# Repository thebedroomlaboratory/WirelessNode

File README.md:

WirelessNode
============

Common code for wireless home automation nodes

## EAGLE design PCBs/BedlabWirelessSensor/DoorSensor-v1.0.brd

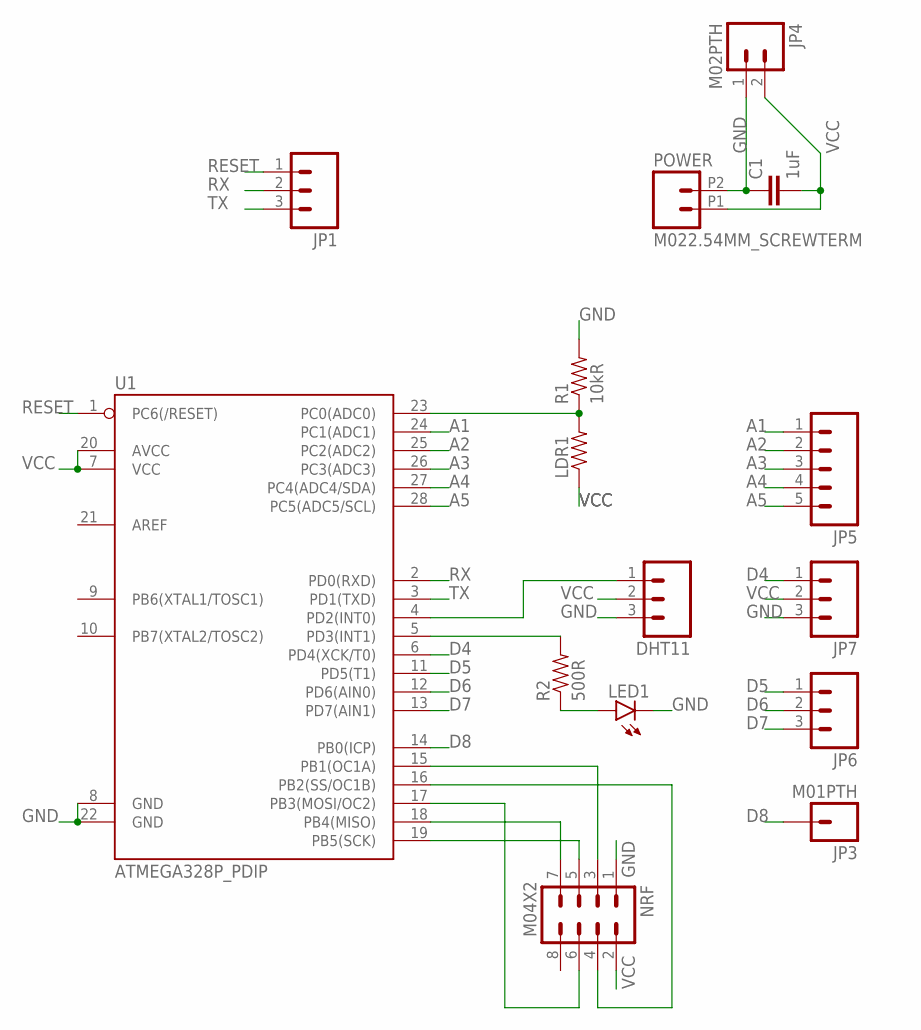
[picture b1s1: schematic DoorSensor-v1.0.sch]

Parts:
C1: 1uF; CAP-PTH-SMALL
DHT11: M03PTH; 1X03
JP1, JP6, JP7: M03PTH; 1X03
JP3: M01PTH; 1X01
JP4: M02PTH; 1X02
JP5: M05PTH; 1X05
LDR1: RESISTORKIT; AXIAL-0.3-KIT
LED1: LED3MM
NRF: M04X2; 2X4
POWER: M022.54MM_SCREWTERM; 1X02_2.54_SCREWTERM
R1: 10kR; AXIAL-0.3-KIT
R2: 500R; AXIAL-0.3-KIT
U1: ATMEGA328P_PDIP; DIL28-3

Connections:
A1: JP5.1, U1.24 (PC1(ADC1))
A2: JP5.2, U1.25 (PC2(ADC2))
A3: JP5.3, U1.26 (PC3(ADC3))
A4: JP5.4, U1.27 (PC4(ADC4/SDA))
A5: JP5.5, U1.28 (PC5(ADC5/SCL))
D4: JP7.1, U1.6 (PD4(XCK/T0))
D5: JP6.1, U1.11 (PD5(T1))
D6: JP6.2, U1.12 (PD6(AIN0))
D7: JP6.3, U1.13 (PD7(AIN1))
D8: JP3.1, U1.14 (PB0(ICP))
GND: C1.1, DHT11.3, JP4.1, JP7.3, LED1.K (C), NRF.1, POWER.P2 (2), R1.P$2 (2), U1.8 (GND), U1.22 (GND)
unnamed: LDR1.P$2 (2), R1.P$1 (1), U1.23 (PC0(ADC0))
unnamed: LED1.A, R2.P$1 (1)
unnamed: DHT11.1, U1.4 (PD2(INT0))
unnamed: R2.P$2 (2), U1.5 (PD3(INT1))
unnamed: NRF.3, U1.15 (PB1(OC1A))
unnamed: NRF.4, U1.16 (PB2(SS/OC1B))
unnamed: NRF.5, U1.19 (PB5(SCK))
unnamed: NRF.7, U1.18 (PB4(MISO))
unnamed: NRF.6, U1.17 (PB3(MOSI/OC2))
RESET: JP1.1, U1.1 (PC6(/RESET))
RX: JP1.2, U1.2 (PD0(RXD))
TX: JP1.3, U1.3 (PD1(TXD))
VCC: C1.2, DHT11.2, JP4.2, JP7.2, LDR1.P$1 (1), NRF.2, POWER.P1 (1), U1.7 (VCC), U1.20 (AVCC)

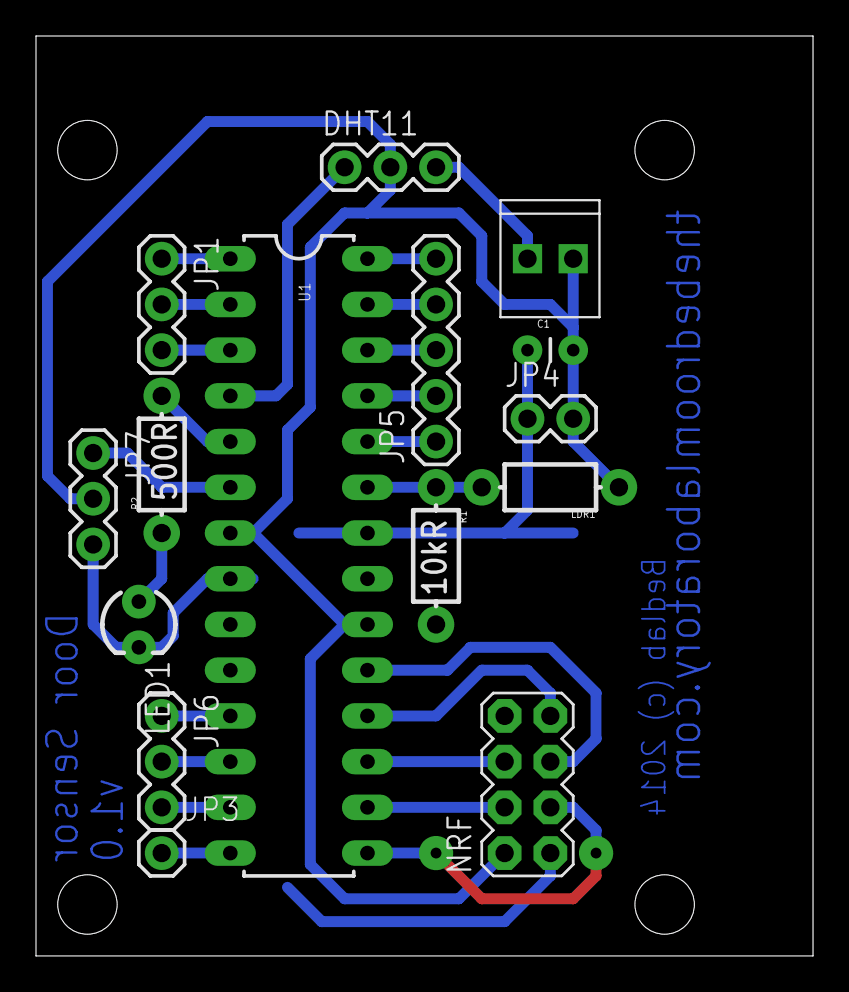
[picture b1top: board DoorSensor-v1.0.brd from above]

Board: 2 copper layers, 43.2 x 51.1 mm, 19 parts (0 on the bottom side), 24 nets.

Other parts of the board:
U$1, U$2, U$3, U$4: STAND-OFF

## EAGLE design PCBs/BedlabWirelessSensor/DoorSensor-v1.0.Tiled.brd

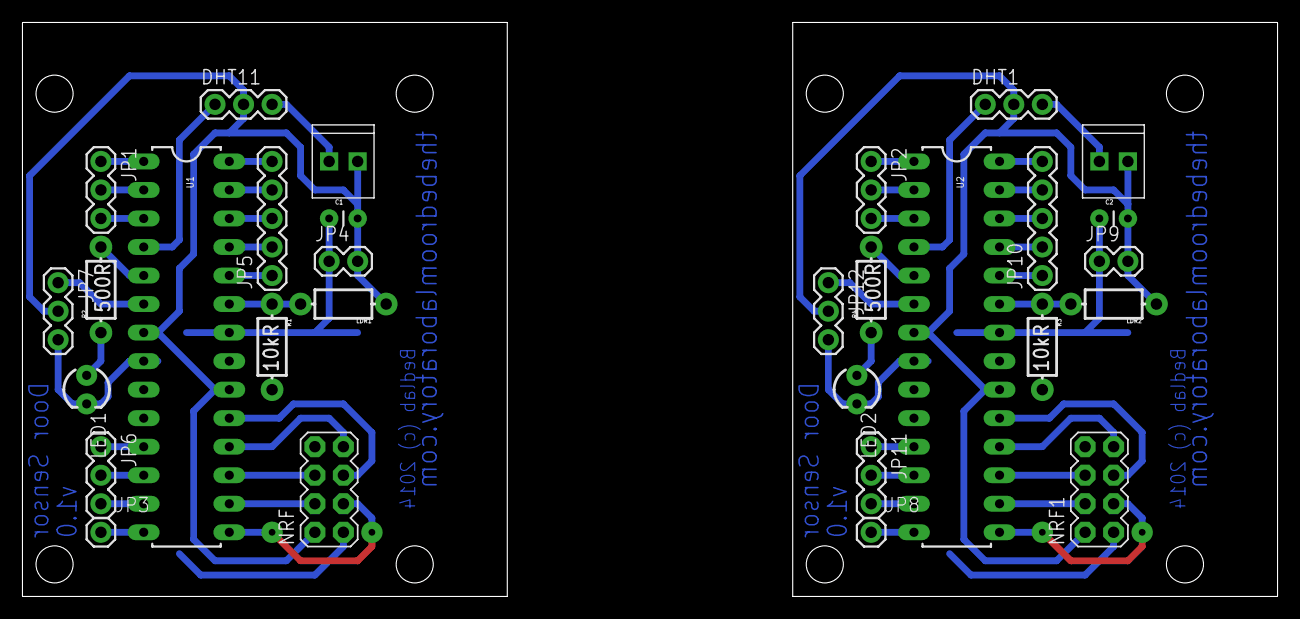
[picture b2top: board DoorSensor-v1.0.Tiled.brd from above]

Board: 2 copper layers, 111.7 x 51.1 mm, 38 parts (0 on the bottom side), 48 nets.

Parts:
C1, C2: 1uF; CAP-PTH-SMALL
DHT1, DHT11: 1X03
JP1, JP2, JP6, JP7, JP11, JP12: 1X03
JP3, JP8: M01PTH; 1X01
JP4, JP9: M02PTH; 1X02
JP5, JP10: 1X05
LDR1, LDR2: AXIAL-0.3-KIT
LED1, LED2: LED3MM
NRF, NRF1: M04X2; 2X4
POWER, POWER1: M022.54MM_SCREWTERM; 1X02_2.54_SCREWTERM
R1, R3: 10kR; AXIAL-0.3-KIT
R2, R4: 500R; AXIAL-0.3-KIT
U1, U2: ATMEGA328P_PDIP; DIL28-3
U$1, U$2, U$3, U$4, U$5, U$6, U$7, U$8: STAND-OFF

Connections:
A1: JP5.1, U1.24
A2: JP5.2, U1.25
A3: JP5.3, U1.26
A4: JP5.4, U1.27
A5: JP5.5, U1.28
A6: JP10.1, U2.24
A7: JP10.2, U2.25
A8: JP10.3, U2.26
A9: JP10.4, U2.27
A10: JP10.5, U2.28
D1: JP8.1, U2.14
D2: JP12.1, U2.6
D3: JP11.1, U2.11
D4: JP7.1, U1.6
D5: JP6.1, U1.11
D6: JP6.2, U1.12
D7: JP6.3, U1.13
D8: JP3.1, U1.14
D9: JP11.2, U2.12
D10: JP11.3, U2.13
GND: C1.1, DHT11.3, JP4.1, JP7.3, LED1.K, NRF.1, POWER.P2, R1.P$2, U1.8, U1.22
GND1: C2.1, DHT1.3, JP9.1, JP12.3, LED2.K, NRF1.1, POWER1.P2, R3.P$2, U2.8, U2.22
unnamed: LDR1.P$2, R1.P$1, U1.23
unnamed: LED1.A, R2.P$1
unnamed: DHT11.1, U1.4
unnamed: R2.P$2, U1.5
unnamed: NRF.3, U1.15
unnamed: NRF.4, U1.16
unnamed: NRF.5, U1.19
unnamed: LDR2.P$2, R3.P$1, U2.23
unnamed: NRF.7, U1.18
unnamed: NRF.6, U1.17
unnamed: LED2.A, R4.P$1
unnamed: R4.P$2, U2.5
unnamed: NRF1.3, U2.15
unnamed: NRF1.4, U2.16
unnamed: NRF1.5, U2.19
unnamed: NRF1.7, U2.18
unnamed: NRF1.6, U2.17
unnamed: DHT1.1, U2.4
RESET: JP1.1, U1.1
RESET1: JP2.1, U2.1
RX: JP1.2, U1.2
RX1: JP2.2, U2.2
TX: JP1.3, U1.3
TX1: JP2.3, U2.3
VCC: C1.2, DHT11.2, JP4.2, JP7.2, LDR1.P$1, NRF.2, POWER.P1, U1.7, U1.20
VCC1: C2.2, DHT1.2, JP9.2, JP12.2, LDR2.P$1, NRF1.2, POWER1.P1, U2.7, U2.20

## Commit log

2014-07-19 Very rough first commit for arduino wireless sensors. The structure of the sketch is that there should be a profile for each type of sensor and each node is setup for wireless connectivity too, on th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
    Code needs a good bit of tidying and fixing but thought it might be good to commit before it gets deleted accidentally or something.
2014-07-19 Victor's code for power strip added from Maker 2014 repository
2014-07-19 Added schematic and PCB drawings for wireless sensors. Designs for power strip still need to be done.
2014-07-19 Restructuring of file structure
2014-07-20 Tiled PCB layout added for printing tomorrow. Additionally, changes made to arduino sketches to add funtionality for LDR, LED, Temp/humid sensor and switching the lights on/off from the gateway.
2014-07-20 Added code for gateway node, needs to be migrated over to Galileo.
2014-07-20 Working basenode code for sending light switching orders to different zones.
2014-07-20 added sketch nrf and relay code
2014-07-20 added raw code for sensors requires cleanup
2014-07-24 Changed library for the DHT11 sensor so that it works with the internal oscilator of the 328p as a clock source.
2014-07-26 Set relay node correctly to 4
2014-07-26 added CT readings
2014-07-26 Added code to update relays from server input
2014-07-26 Updated baseNode.ino to communicate with both the power strip and the wireless sensors. It uses the node address to configure the communication protocol.
2014-07-26 Updated code to send serial data to RPi in format required for REST service. Also fixed code for wireless sensors to set up the right struct format.
2014-07-26 Added python server code
2014-07-26 added some checks and relays

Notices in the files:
PCBs/BedlabWirelessSensor/DoorSensor-v1.0.Tiled.brd:
Bedlab (c) 2014
parts and their libraries:
SparkFun-Passives: Licensing: Creative Commons ShareAlike 4.0 International - https://creativecommons.org/licenses/by-sa/4.0
